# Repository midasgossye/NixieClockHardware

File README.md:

# NixieClockHardware
6 digit RPi powered Nixie Clock Hardware repository

Software/source code can be found in the following repository: https://github.com/midasgossye/NixieClock/

If you are interested in a having this unique Nixie Clock, but don't want to build it from scratch, we sell these at our tindie store!

/i/92521/products/2019-04-29T16%3A27%3A55.943Z-nixie2.jpg)

## Authors

* **Midas Gossye** - [Github](https://github.com/midasgossye)
* **Joshua Spaander** - [Github](https://github.com/joshuaspaander)

## Acknowledgments

* This project was inspired by and partly based on the New Precise Nixie Clock from the May 2016 issue of Elektor Magazine [(link)](https://www.elektormagazine.com/magazine/elektor-201605/28960)
* IoT connectivity inspired by EEVBlog Nixie Tube Display Project [(link)](https://www.youtube.com/playlist?list=PLvOlSehNtuHutdg1kZkG7aAYhjoJnk2fc)

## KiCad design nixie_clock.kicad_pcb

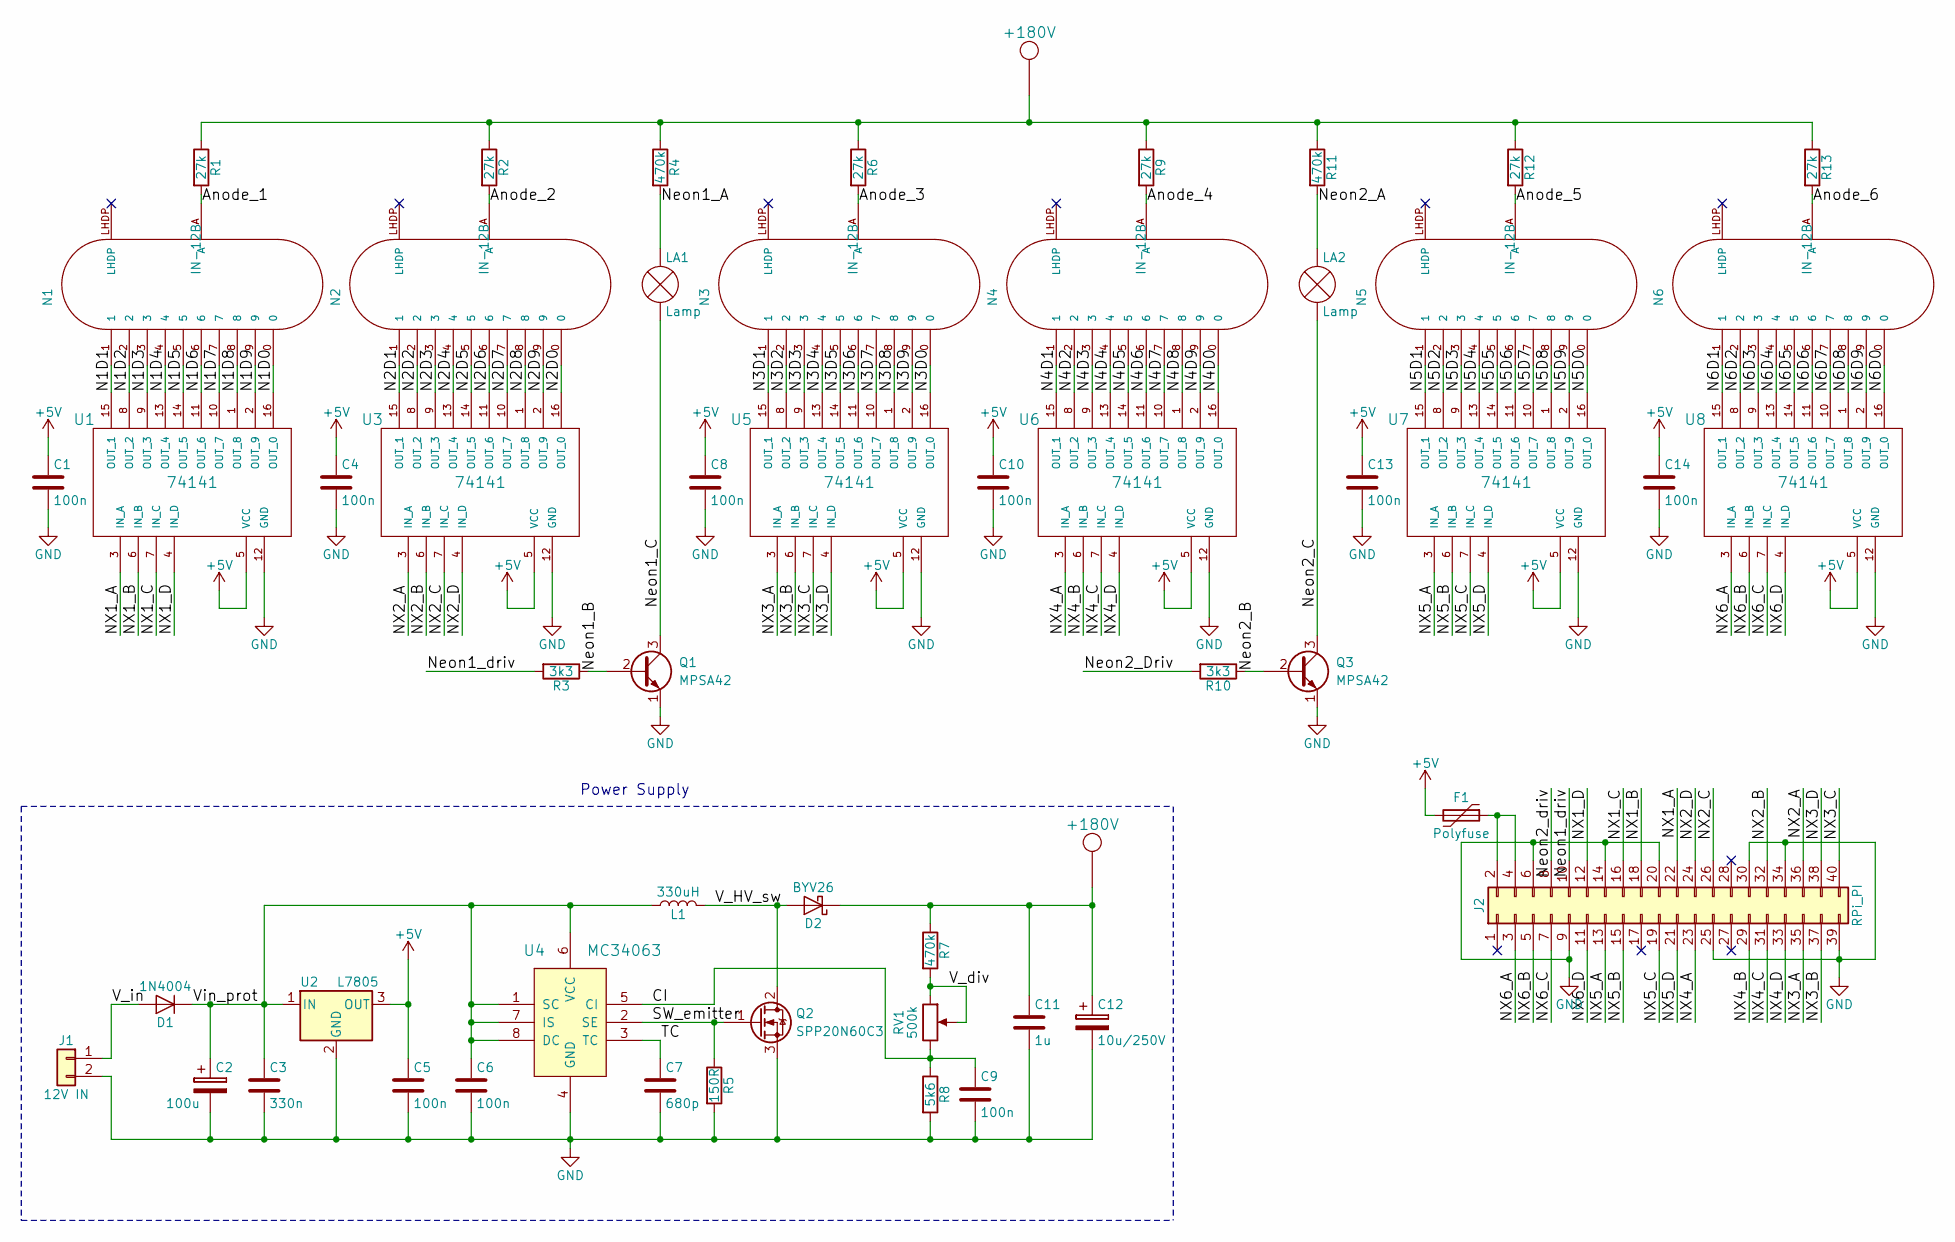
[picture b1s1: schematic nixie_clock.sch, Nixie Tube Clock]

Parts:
C1, C4, C5, C6, C8, C9, C10, C13, C14: 100n; C_1206_HandSoldering
C2: 100u; CP_Radial_D6.3mm_P2.50mm
C3: 330n; C_1206_HandSoldering
C7: 680p; C_0805_HandSoldering
C11: 1u; C_Rect_L18.0mm_W11.0mm_P15.00mm_FKS3_FKP3
C12: 10u/250V; CP_Radial_D10.0mm_P5.00mm
D1: 1N4004; D_DO-41_SOD81_P10.16mm_Horizontal
D2: BYV26; SOD-57
F1: Polyfuse; R_1206_HandSoldering
J1: 12V IN; BARREL_JACK
J2: RPi_PI; RPi-zero
L1: 330uH; SMDRI127
LA1, LA2: Lamp; Pin_Header_Straight_1x02_Pitch2.54mm
N1, N2, N3, N4, N5, N6: IN-12B; IN-12
Q1, Q3: MPSA42; TO-92_Inline_Narrow_Oval
Q2: SPP20N60C3; TO-220-3_Vertical
R1, R2, R6, R9, R12, R13: 27k; R_Axial_DIN0207_L6.3mm_D2.5mm_P10.16mm_Horizontal
R3, R10: 3k3; R_Axial_DIN0207_L6.3mm_D2.5mm_P10.16mm_Horizontal
R4, R7, R11: 470k; R_Axial_DIN0207_L6.3mm_D2.5mm_P15.24mm_Horizontal
R5: 150R; R_1206_HandSoldering
R8: 5k6; R_Axial_DIN0207_L6.3mm_D2.5mm_P10.16mm_Horizontal
RV1: 500k; 3362P
U1, U3, U5, U6, U7, U8: 74141; DIP-16_W7.62mm_Socket
U2: L7805; TO-220-3_Vertical
U4: MC34063; DIP-8_W7.62mm

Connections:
+5V: C1.1, C4.1, C5.1, C8.1, C10.1, C13.1, C14.1, F1.2, U1.5 (VCC), U2.3 (OUT), U3.5 (VCC), U5.5 (VCC), U6.5 (VCC), U7.5 (VCC), U8.5 (VCC)
+180V: C11.1, C12.1, D2.1 (K), R1.1, R2.1, R4.1, R6.1, R7.1, R9.1, R11.1, R12.1, R13.1
/Anode_1: N1.A, R1.2
/Anode_2: N2.A, R2.2
/Anode_3: N3.A, R6.2
/Anode_4: N4.A, R9.2
/Anode_5: N5.A, R12.2
/Anode_6: N6.A, R13.2
/CI: C9.1, R8.1, RV1.3, U4.5 (CI)
/N1D0: N1.0, U1.16 (OUT_0)
/N1D1: N1.1, U1.15 (OUT_1)
/N1D2: N1.2, U1.8 (OUT_2)
/N1D3: N1.3, U1.9 (OUT_3)
/N1D4: N1.4, U1.13 (OUT_4)
/N1D5: N1.5, U1.14 (OUT_5)
/N1D6: N1.6, U1.11 (OUT_6)
/N1D7: N1.7, U1.10 (OUT_7)
/N1D8: N1.8, U1.1 (OUT_8)
/N1D9: N1.9, U1.2 (OUT_9)
/N2D0: N2.0, U3.16 (OUT_0)
/N2D1: N2.1, U3.15 (OUT_1)
/N2D2: N2.2, U3.8 (OUT_2)
/N2D3: N2.3, U3.9 (OUT_3)
/N2D4: N2.4, U3.13 (OUT_4)
/N2D5: N2.5, U3.14 (OUT_5)
/N2D6: N2.6, U3.11 (OUT_6)
/N2D7: N2.7, U3.10 (OUT_7)
/N2D8: N2.8, U3.1 (OUT_8)
/N2D9: N2.9, U3.2 (OUT_9)
/N3D0: N3.0, U5.16 (OUT_0)
/N3D1: N3.1, U5.15 (OUT_1)
/N3D2: N3.2, U5.8 (OUT_2)
/N3D3: N3.3, U5.9 (OUT_3)
/N3D4: N3.4, U5.13 (OUT_4)
/N3D5: N3.5, U5.14 (OUT_5)
/N3D6: N3.6, U5.11 (OUT_6)
/N3D7: N3.7, U5.10 (OUT_7)
/N3D8: N3.8, U5.1 (OUT_8)
/N3D9: N3.9, U5.2 (OUT_9)
/N4D0: N4.0, U6.16 (OUT_0)
/N4D1: N4.1, U6.15 (OUT_1)
/N4D2: N4.2, U6.8 (OUT_2)
/N4D3: N4.3, U6.9 (OUT_3)
/N4D4: N4.4, U6.13 (OUT_4)
/N4D5: N4.5, U6.14 (OUT_5)
/N4D6: N4.6, U6.11 (OUT_6)
/N4D7: N4.7, U6.10 (OUT_7)
/N4D8: N4.8, U6.1 (OUT_8)
/N4D9: N4.9, U6.2 (OUT_9)
/N5D0: N5.0, U7.16 (OUT_0)
/N5D1: N5.1, U7.15 (OUT_1)
/N5D2: N5.2, U7.8 (OUT_2)
/N5D3: N5.3, U7.9 (OUT_3)
/N5D4: N5.4, U7.13 (OUT_4)
/N5D5: N5.5, U7.14 (OUT_5)
/N5D6: N5.6, U7.11 (OUT_6)
/N5D7: N5.7, U7.10 (OUT_7)
/N5D8: N5.8, U7.1 (OUT_8)
/N5D9: N5.9, U7.2 (OUT_9)
/N6D0: N6.0, U8.16 (OUT_0)
/N6D1: N6.1, U8.15 (OUT_1)
/N6D2: N6.2, U8.8 (OUT_2)
/N6D3: N6.3, U8.9 (OUT_3)
/N6D4: N6.4, U8.13 (OUT_4)
/N6D5: N6.5, U8.14 (OUT_5)
/N6D6: N6.6, U8.11 (OUT_6)
/N6D7: N6.7, U8.10 (OUT_7)
/N6D8: N6.8, U8.1 (OUT_8)
/N6D9: N6.9, U8.2 (OUT_9)
/NX1_A: J2.22, U1.3 (IN_A)
/NX1_B: J2.18, U1.6 (IN_B)
/NX1_C: J2.16, U1.7 (IN_C)
/NX1_D: J2.12, U1.4 (IN_D)
/NX2_A: J2.36, U3.3 (IN_A)
/NX2_B: J2.32, U3.6 (IN_B)
/NX2_C: J2.26, U3.7 (IN_C)
/NX2_D: J2.24, U3.4 (IN_D)
/NX3_A: J2.35, U5.3 (IN_A)
/NX3_B: J2.37, U5.6 (IN_B)
/NX3_C: J2.40, U5.7 (IN_C)
/NX3_D: J2.38, U5.4 (IN_D)
/NX4_A: J2.23, U6.3 (IN_A)
/NX4_B: J2.29, U6.6 (IN_B)
/NX4_C: J2.31, U6.7 (IN_C)
/NX4_D: J2.33, U6.4 (IN_D)
/NX5_A: J2.13, U7.3 (IN_A)
/NX5_B: J2.15, U7.6 (IN_B)
/NX5_C: J2.19, U7.7 (IN_C)
/NX5_D: J2.21, U7.4 (IN_D)
/NX6_A: J2.3, U8.3 (IN_A)
/NX6_B: J2.5, U8.6 (IN_B)
/NX6_C: J2.7, U8.7 (IN_C)
/NX6_D: J2.11, U8.4 (IN_D)
/Neon1_A: LA1.2 (+), R4.2
/Neon1_B: Q1.2 (B), R3.1
/Neon1_C: LA1.1 (-), Q1.3 (C)
/Neon1_driv: J2.10, R3.2
/Neon2_A: LA2.2 (+), R11.2
/Neon2_B: Q3.2 (B), R10.1
/Neon2_C: LA2.1 (-), Q3.3 (C)
/Neon2_Driv: J2.8, R10.2
/SW_emitter: Q2.1 (G), R5.1, U4.2 (SE)
/TC: C7.1, U4.3 (TC)
/V_HV_sw: D2.2 (A), L1.2, Q2.2 (D)
/V_div: R7.2, RV1.1, RV1.2
/V_in: D1.2 (A), J1.1
/Vin_prot: C2.1, C3.1, C6.1, D1.1 (K), L1.1, U2.1 (IN), U4.1 (SC), U4.6 (VCC), U4.7 (IS), U4.8 (DC)
GND: C1.2, C2.2, C3.2, C4.2, C5.2, C6.2, C7.2, C8.2, C9.2, C10.2, C11.2, C12.2, C13.2, C14.2, J1.2, J2.6, J2.9, J2.14, J2.20, J2.25, J2.30, J2.34, J2.39, Q1.1 (E), Q2.3 (S), Q3.1 (E), R5.2, R8.2, U1.12 (GND), U2.2 (GND), U3.12 (GND), U4.4 (GND), U5.12 (GND), U6.12 (GND), U7.12 (GND), U8.12 (GND)
unnamed: F1.1, J2.2, J2.4

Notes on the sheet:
Power Supply

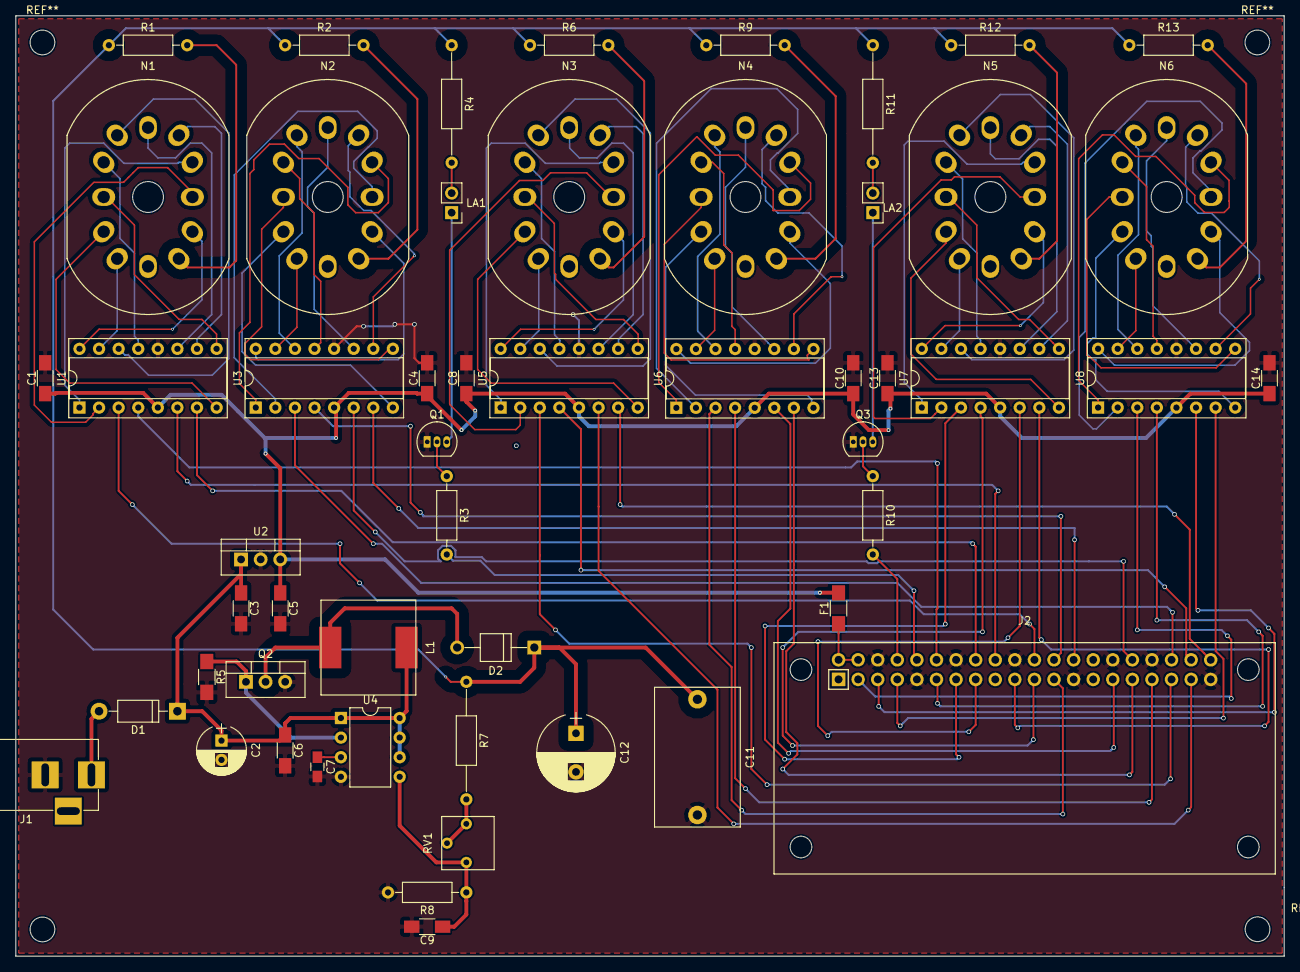
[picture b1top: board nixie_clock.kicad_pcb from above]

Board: 2 copper layers, 164.5 x 121.9 mm, 53 parts (0 on the bottom side), 109 nets.

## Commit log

2019-07-02 Added png schematic
2019-07-18 Added picture
2019-07-18 Added link to SW repo
